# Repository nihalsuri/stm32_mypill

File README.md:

# stm32_mypill
Personal take on the STM32 line of pill devices 

* This project is made in KiCAD 6.0 and is a basic and simple breakout board for the STM32F103C8T6. 

* All the files required for manafacturing purposes are in the "manafacturing" folder which is a part of the **stm32myPill** directory. 

# Schematic

# PCB

# 3D View

# Final Product

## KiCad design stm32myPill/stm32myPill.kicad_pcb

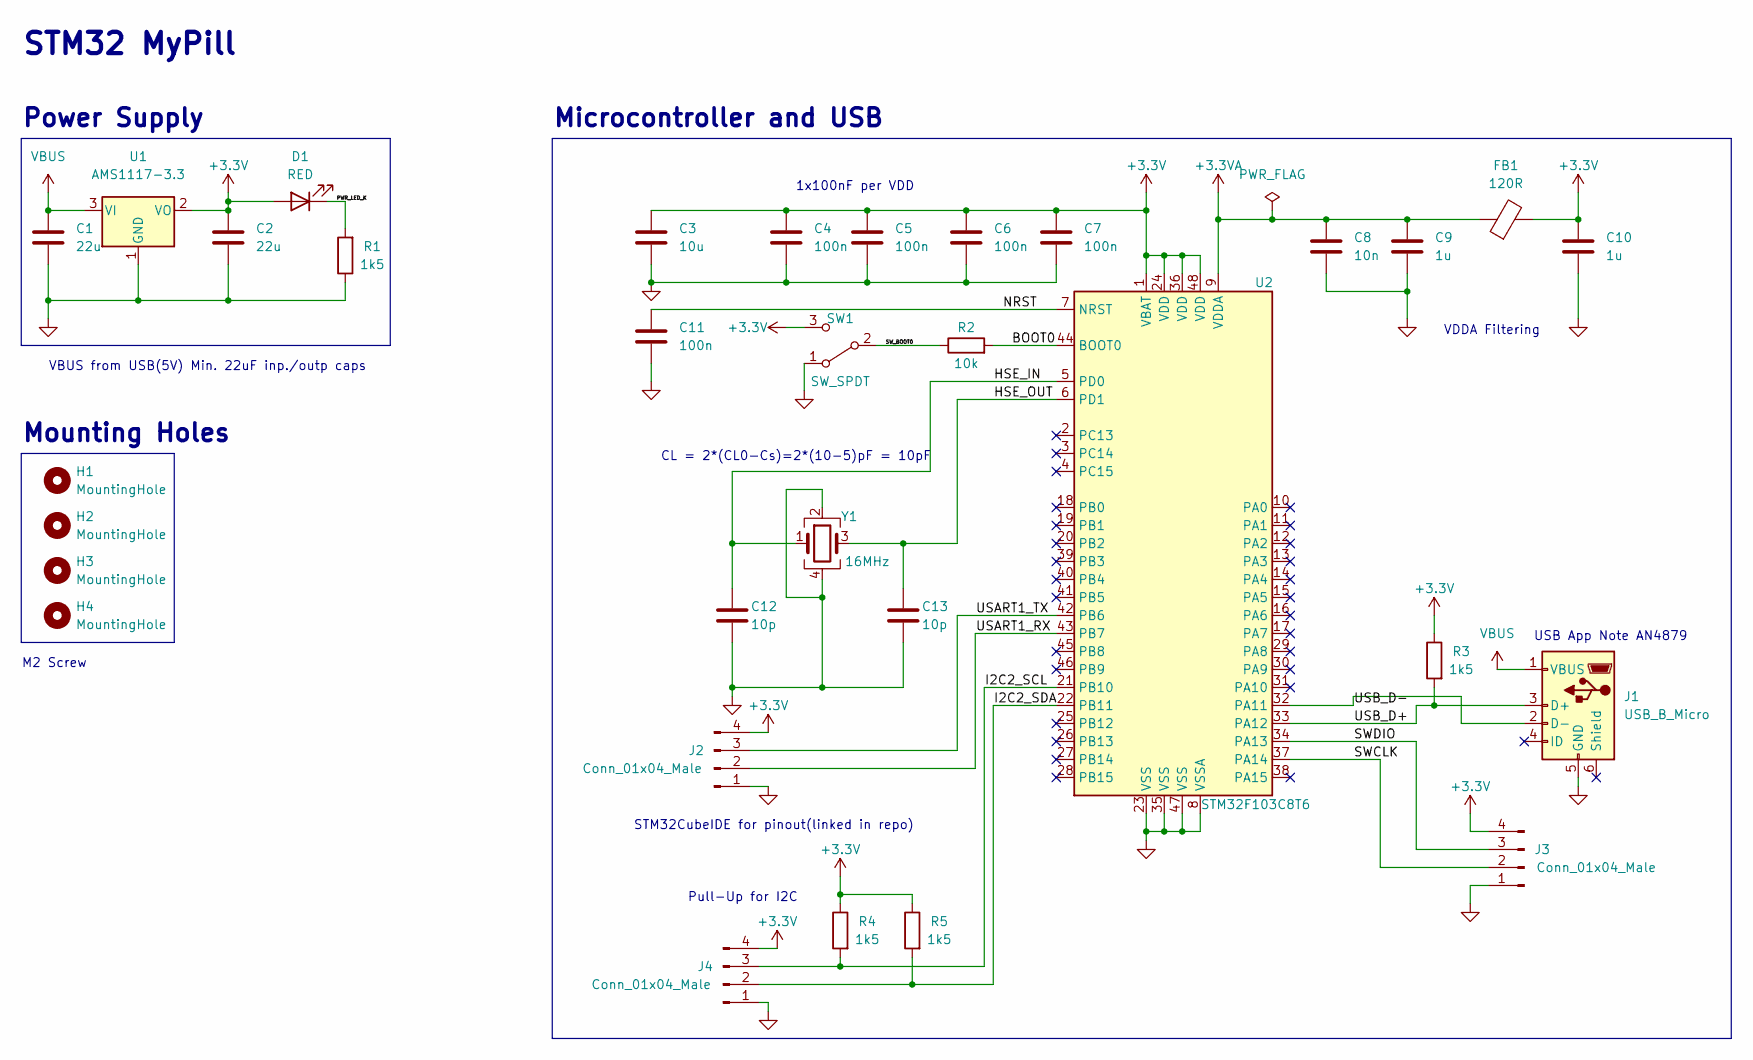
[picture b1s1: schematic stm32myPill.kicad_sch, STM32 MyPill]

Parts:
C1, C2: 22u; C_0805_2012Metric
C3: 10u; C_0603_1608Metric
C4, C5, C6, C7, C11: 100n; C_0402_1005Metric
C8: 10n; C_0402_1005Metric
C9, C10: 1u; C_0402_1005Metric
C12, C13: 10p; C_0402_1005Metric
D1: RED; LED_0603_1608Metric
FB1: 120R; L_0603_1608Metric
H1, H2, H3, H4: MountingHole; MountingHole_2.2mm_M2
J1: USB_B_Micro; USB_Micro-B_Wuerth_629105150521
J2, J3, J4: Conn_01x04_Male; PinHeader_1x04_P2.54mm_Vertical
R1, R3, R4, R5: 1k5; R_0402_1005Metric
R2: 10k; R_0402_1005Metric
SW1: SW_SPDT; SW_SPDT_PCM12
U1: AMS1117-3.3; SOT-223-3_TabPin2
U2: STM32F103C8T6; LQFP-48_7x7mm_P0.5mm
Y1: 16MHz; Crystal_SMD_3225-4Pin_3.2x2.5mm

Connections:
+3.3VA: C8.1, C9.1, FB1.1, U2.9 (VDDA)
+3V3: C2.1, C3.1, C4.1, C5.1, C6.1, C7.1, C10.1, D1.2 (A), FB1.2, J2.4, J3.4, J4.4, R3.1, R4.1, R5.1, SW1.3 (C), U1.2 (VO), U2.1 (VBAT), U2.24 (VDD), U2.36 (VDD), U2.48 (VDD)
/BOOT0: R2.2, U2.44 (BOOT0)
/HSE_IN: C12.1, U2.5 (PD0), Y1.1
/HSE_OUT: C13.1, U2.6 (PD1), Y1.3
/I2C2_SCL: J4.3, R4.2, U2.21 (PB10)
/I2C2_SDA: J4.2, R5.2, U2.22 (PB11)
/NRST: C11.1, U2.7 (NRST)
/PWR_LED_K: D1.1 (K), R1.2
/SWCLK: J3.2, U2.37 (PA14)
/SWDIO: J3.3, U2.34 (PA13)
/SW_BOOT0: R2.1, SW1.2 (B)
/USART1_RX: J2.2, U2.43 (PB7)
/USART1_TX: J2.3, U2.42 (PB6)
/USB_D+: J1.3 (D+), R3.2, U2.33 (PA12)
/USB_D-: J1.2 (D-), U2.32 (PA11)
GND: C1.2, C2.2, C3.2, C4.2, C5.2, C6.2, C7.2, C8.2, C9.2, C10.2, C11.2, C12.2, C13.2, J1.5 (GND), J2.1, J3.1, J4.1, R1.1, SW1.1 (A), U1.1 (GND), U2.8 (VSSA), U2.23 (VSS), U2.35 (VSS), U2.47 (VSS), Y1.2, Y1.4
VBUS: C1.1, J1.1 (VBUS), U1.3 (VI)

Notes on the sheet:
STM32 MyPill
Pull-Up for I2C
Mounting Holes
CL = 2*(CL0-Cs)=2*(10-5)pF = 10pF
VDDA Filtering
Power Supply
USB App Note AN4879
1x100nF per VDD
STM32CubeIDE for pinout(linked in repo)
M2 Screw
Microcontroller and USB
VBUS from USB(5V) Min. 22uF inp./outp caps

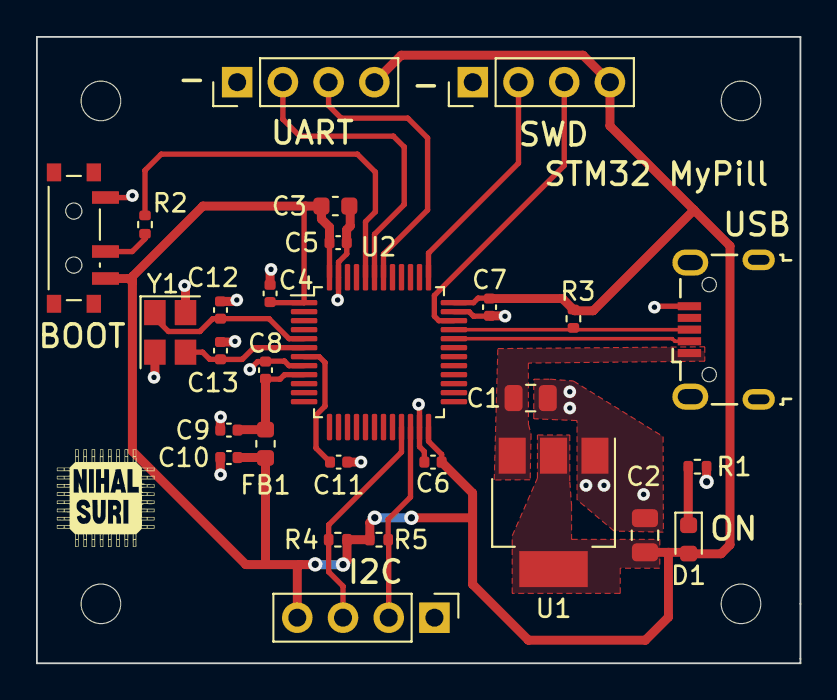
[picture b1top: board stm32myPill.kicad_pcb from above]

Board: 2 copper layers, 42.4 x 34.8 mm, 32 parts (0 on the bottom side), 18 nets.

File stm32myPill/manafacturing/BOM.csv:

"Ref","Qnty","Value","Cmp name","Footprint","Description","Vendor"
"C1, C2, ","2","22u","C","Capacitor_SMD:C_0805_2012Metric","Unpolarized capacitor",""
"C3, ","1","10u","C","Capacitor_SMD:C_0603_1608Metric","Unpolarized capacitor",""
"C4, C5, C6, C7, C11, ","5","100n","C","Capacitor_SMD:C_0402_1005Metric","Unpolarized capacitor",""
"C8, ","1","10n","C","Capacitor_SMD:C_0402_1005Metric","Unpolarized capacitor",""
"C9, C10, ","2","1u","C","Capacitor_SMD:C_0402_1005Metric","Unpolarized capacitor",""
"C12, C13, ","2","10p","C","Capacitor_SMD:C_0402_1005Metric","Unpolarized capacitor",""
"D1, ","1","RED","LED","LED_SMD:LED_0603_1608Metric","Light emitting diode",""
"FB1, ","1","120R","FerriteBead","Inductor_SMD:L_0603_1608Metric","Ferrite bead",""
"J1, ","1","USB_B_Micro","USB_B_Micro","Connector_USB:USB_Micro-B_Wuerth_629105150521","USB Micro Type B connector",""
"J2, J3, J4, ","3","Conn_01x04_Male","Conn_01x04_Male","Connector_PinHeader_2.54mm:PinHeader_1x04_P2.54mm_Vertical","Generic connector, single row, 01x04, script generated (kicad-library-utils/schlib/autogen/connector/)",""
"R1, R3, R4, R5, ","4","1k5","R","Resistor_SMD:R_0402_1005Metric","Resistor",""
"R2, ","1","10k","R","Resistor_SMD:R_0402_1005Metric","Resistor",""
"SW1, ","1","SW_SPDT","SW_SPDT","Button_Switch_SMD:SW_SPDT_PCM12","Switch, single pole double throw",""
"U1, ","1","AMS1117-3.3","AMS1117-3.3","Package_TO_SOT_SMD:SOT-223-3_TabPin2","1A Low Dropout regulator, positive, 3.3V fixed output, SOT-223",""
"U2, ","1","STM32F103C8T6","STM32F103C8Tx","Package_QFP:LQFP-48_7x7mm_P0.5mm","ARM Cortex-M3 MCU, 64KB flash, 20KB RAM, 72MHz, 2-3.6V, 37 GPIO, LQFP-48",""
"Y1, ","1","16MHz","Crystal_GND24","Crystal:Crystal_SMD_3225-4Pin_3.2x2.5mm","Four pin crystal, GND on pins 2 and 4",""

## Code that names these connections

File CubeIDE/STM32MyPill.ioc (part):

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Mcu.Name=STM32F103C(8-B)Tx
Mcu.Package=LQFP48
Mcu.UserName=STM32F103C8Tx
PA1.Signal=S_TIM2_CH2
PA11.Mode=Device
PA11.Signal=USB_DM
PA12.Mode=Device
PA12.Signal=USB_DP
PA13.Mode=Serial_Wire
PA13.Signal=SYS_JTMS-SWDIO
PA14.Mode=Serial_Wire
PA14.Signal=SYS_JTCK-SWCLK
PA3.Signal=ADCx_IN3
PB10.Mode=I2C
PB10.Signal=I2C2_SCL
PB11.Mode=I2C
PB11.Signal=I2C2_SDA
PB6.Mode=Asynchronous
PB6.Signal=USART1_TX
PB7.Mode=Asynchronous
PB7.Signal=USART1_RX
PD0-OSC_IN.Mode=HSE-External-Oscillator
PD0-OSC_IN.Signal=RCC_OSC_IN
PD1-OSC_OUT.Mode=HSE-External-Oscillator
PD1-OSC_OUT.Signal=RCC_OSC_OUT
RCC.SYSCLKFreq_VALUE=48000000
RCC.SYSCLKSource=RCC_SYSCLKSOURCE_PLLCLK
board=custom

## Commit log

2022-02-11 added CubeIDE and finished MCU schematic
2022-02-13 changed IOC file for pinout
2022-02-13 completed sch and added footprints
2022-02-14 finished layout added mounting holes
2022-02-14 3D Model for USB
2022-02-22 finished pcb
2022-02-23 added manafacturing files
2022-02-23 added photos
2022-03-03 xml files
